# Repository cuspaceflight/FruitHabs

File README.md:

# Sunrise
Simple Raspberry Pi Pico based flight computer for HABs

## Features
- GPS
- Radio communication via LoRa
- SD card logging
- Temperature recording

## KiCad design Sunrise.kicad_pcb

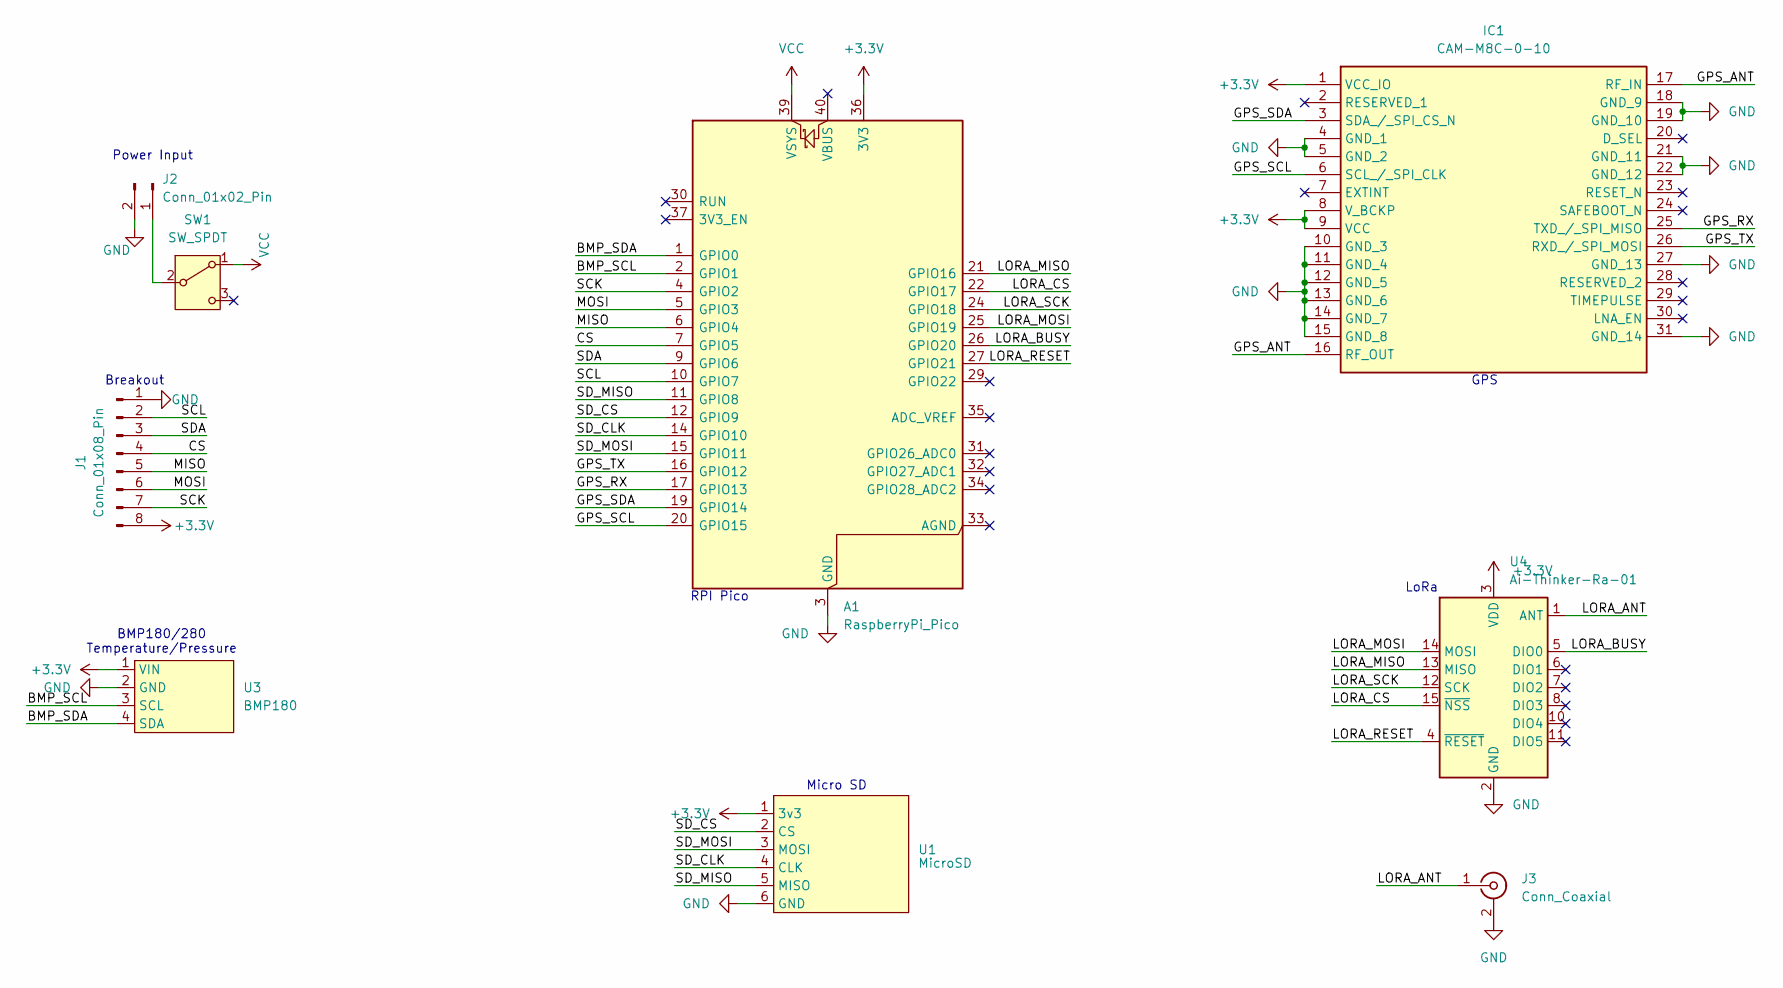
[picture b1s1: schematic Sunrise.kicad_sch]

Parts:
A1: RaspberryPi_Pico; RaspberryPi_Pico_Common_Unspecified
IC1: CAM-M8C-0-10; CAMM8C010; Manufacturer_Part_Number CAM-M8C-0-10
J1: Conn_01x08_Pin; PinSocket_1x08_P2.54mm_Vertical
J2: Conn_01x02_Pin; PinSocket_1x02_P2.54mm_Vertical
J3: Conn_Coaxial; SMA_Amphenol_901-143_Horizontal
SW1: SW_SPDT; SW_Slide_SPDT_Angled_CK_OS102011MA1Q
U1: MicroSD
U3: BMP180
U4: Ai-Thinker-Ra-01; Ai-Thinker-Ra-01-LoRa

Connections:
+3.3V: A1.36 (3V3), IC1.1 (VCC_IO), IC1.8 (V_BCKP), IC1.9 (VCC), J1.8, U1.1 (3v3), U3.1 (VIN), U4.3 (VDD)
/BMP_SCL: A1.2 (GPIO1), U3.3 (SCL)
/BMP_SDA: A1.1 (GPIO0), U3.4 (SDA)
/CS: A1.7 (GPIO5), J1.4
/GPS_ANT: IC1.16 (RF_OUT), IC1.17 (RF_IN)
/GPS_RX: A1.17 (GPIO13), IC1.25 (TXD_/_SPI_MISO)
/GPS_SCL: A1.20 (GPIO15), IC1.6 (SCL_/_SPI_CLK)
/GPS_SDA: A1.19 (GPIO14), IC1.3 (SDA_/_SPI_CS_N)
/GPS_TX: A1.16 (GPIO12), IC1.26 (RXD_/_SPI_MOSI)
/LORA_ANT: J3.1 (In), U4.1 (ANT)
/LORA_BUSY: A1.26 (GPIO20), U4.5 (DIO0)
/LORA_CS: A1.22 (GPIO17), U4.15 (~NSS)
/LORA_MISO: A1.21 (GPIO16), U4.13 (MISO)
/LORA_MOSI: A1.25 (GPIO19), U4.14 (MOSI)
/LORA_RESET: A1.27 (GPIO21), U4.4 (~RESET)
/LORA_SCK: A1.24 (GPIO18), U4.12 (SCK)
/MISO: A1.6 (GPIO4), J1.5
/MOSI: A1.5 (GPIO3), J1.6
/SCK: A1.4 (GPIO2), J1.7
/SCL: A1.10 (GPIO7), J1.2
/SDA: A1.9 (GPIO6), J1.3
/SD_CLK: A1.14 (GPIO10), U1.4 (CLK)
/SD_CS: A1.12 (GPIO9), U1.2 (CS)
/SD_MISO: A1.11 (GPIO8), U1.5 (MISO)
/SD_MOSI: A1.15 (GPIO11), U1.3 (MOSI)
GND: A1.3 (GND), A1.8 (GND), A1.13 (GND), A1.18 (GND), A1.23 (GND), A1.28 (GND), A1.38 (GND), IC1.4 (GND_1), IC1.5 (GND_2), IC1.10 (GND_3), IC1.11 (GND_4), IC1.12 (GND_5), IC1.13 (GND_6), IC1.14 (GND_7), IC1.15 (GND_8), IC1.18 (GND_9), IC1.19 (GND_10), IC1.21 (GND_11), IC1.22 (GND_12), IC1.27 (GND_13), IC1.31 (GND_14), J1.1, J2.2, J3.2 (Ext), U1.6 (GND), U3.2 (GND), U4.2 (GND), U4.9 (GND), U4.16 (GND)
unnamed: J2.1, SW1.2 (B)
VCC: A1.39 (VSYS), SW1.1 (A)

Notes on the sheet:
Micro SD
RPI Pico
GPS
Breakout
Power Input
LoRa
BMP180/280 Temperature/Pressure

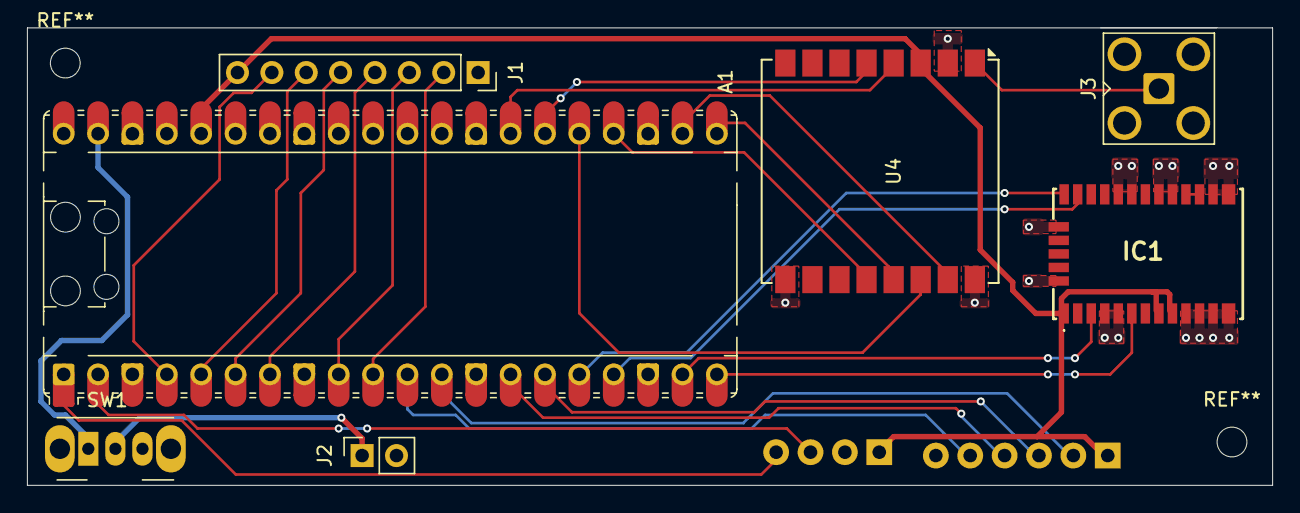
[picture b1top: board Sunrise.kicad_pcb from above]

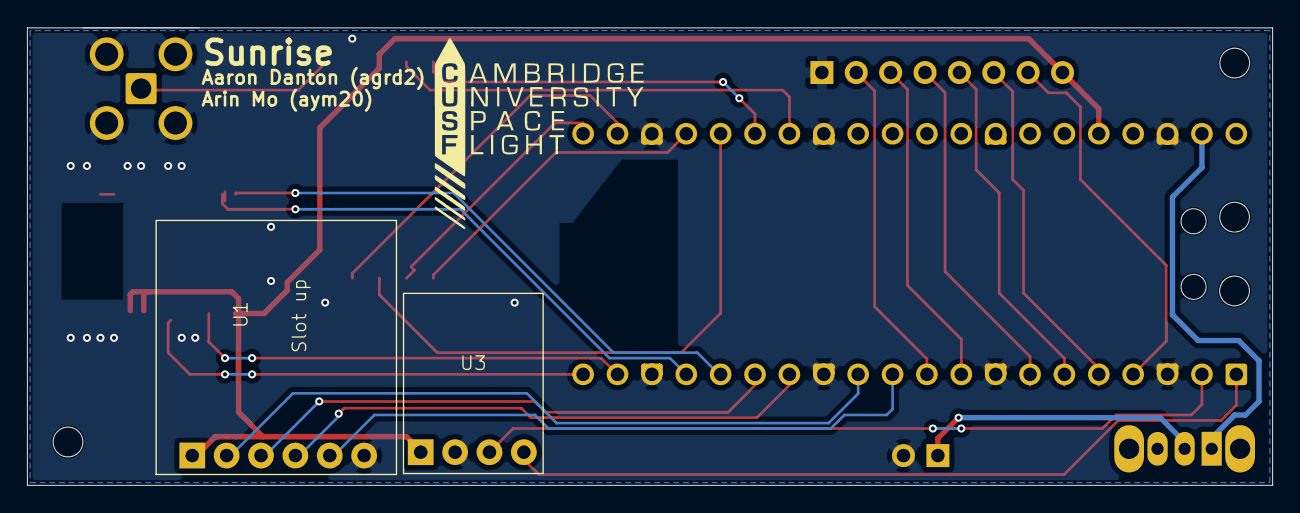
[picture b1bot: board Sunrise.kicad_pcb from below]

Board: 2 copper layers, 91.9 x 33.8 mm, 9 parts (2 on the bottom side), 28 nets.

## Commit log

2026-04-22 WIP: basic schematic
2026-04-22 chore: add README
2026-04-23 feat: initial schematic
2026-04-25 feat: initial PCB layout
2026-05-09 feat: fully wired PCB
2026-05-09 chore: update .gitignore
2026-05-10 feat: added silkscreen
2026-05-10 chore: Rename from Fruit to Sunrise
